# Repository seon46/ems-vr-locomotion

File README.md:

# EMS-VR Locomotion Interface

座位VRユーザーに擬似的な歩行感覚を生成するロコモーションインターフェースの研究プロジェクト。
6チャンネルの下肢EMS（電気筋刺激）と足裏振動を歩行アニメーションに同期させることで、座ったままでも「歩いている」と感じられる体験を目指す。

**埼玉大学大学院 理工学研究科 数理電子情報系専攻 / Parinya Lab — 遠藤 瀬音（Endo Seno）**

## 概要

本研究では、VR空間内の歩行アニメーションに合わせて下肢の筋肉にEMSを与え、歩行に伴う筋収縮感覚を再現する座位向けロコモーションインターフェースを開発しています。

先行研究 LegSense（Um et al., UIST 2024）の歩行感覚EMS提示をベースに、VRアバターのスタミナ低下に連動した疲労感の演出へ拡張することを目指しています。

### 実装済みの機能

- **6チャンネルEMS歩行同期**: Battye et al. (1966) の筋活動データに基づき、歩行アニメーションのNormalized Timeから各筋の収縮タイミングでEMSを発火
- **足裏振動フィードバック**: 4チャンネル（両足の踵・前足部）のERMモーターによる接地感の提示（ファームウェア実装済み、Unity側は未統合）
- **VR歩行環境**: 手続き的生成の廊下シーン、鏡による自己アバター視認、歩行同期のhead bob、足音再生

### 安全基準

- 出力上限: ≤ 10 mA RMS、≤ ±50 V
- 1回の発火は最大1秒（ファームウェアで制限）
- ヒトへの適用前にIRB承認を取得予定

## システム構成

```
┌─────────────────────────────────────────────────────────────┐
│  Unity (PC)                                                 │
│  ├── VR Scene (Meta Quest 3S via Quest Link)                │
│  ├── Walking Animation (Mixamo)                             │
│  ├── EMSTrigger.cs (Normalized Time → 筋活動タイミング発火)  │
│  └── UDP Broadcast (192.168.11.255:8266)                    │
│       ├── "FIRE,l1,l2,l3,l4,l5,l6"  (EMS, Level 0〜15)    │
│       └── "VIB,rh,rf,lh,lf"         (振動, PWM 0〜255)    │
└──────────┬──────────────────────────┬───────────────────────┘
           │                          │
    ┌──────▼──────┐          ┌────────▼────────┐
    │ EMS Module  │          │ Vibration Motor │
    │ ×6 units    │          │ Controller      │
    │             │          │                 │
    │ XIAO        │          │ ESP32 HUZZAH32  │
    │ ESP32-C3    │          │ + IRLZ44N ×4   │
    │ + AC_TENS   │          │ + ERM ×4       │
    │ SHOCK v2    │          │ (Adafruit 1201) │
    └─────────────┘          └─────────────────┘
    大腿四頭筋 (L/R)          右かかと / 右つま先
    ハムストリングス (L/R)     左かかと / 左つま先
    前脛骨筋 (L/R)
```

## ハードウェア

### EMS刺激モジュール（6ch）

| コンポーネント | 説明 |
|---|---|
| XIAO ESP32-C3 × 6 | マイコン（WiFi/UDP受信、IP固定: 192.168.11.101〜106） |
| AC_TENS SHOCK MODULE v2 × 6 | EMS出力モジュール |
| キャリアボード × 6 | KiCad設計、JLCPCB製造 |

### 振動フィードバック（4ch）

| コンポーネント | 説明 |
|---|---|
| Adafruit HUZZAH32 (ESP32 Feather) | マイコン（WiFi/UDP受信・PWM出力） |
| IRLZ44N N-ch MOSFET × 4 | モータードライバ |
| Adafruit 1201 ERM Motor × 4 | φ10mm コイン型振動モーター |
| 1N4148 ダイオード × 4 | フライバック保護 |

### VR

| コンポーネント | 説明 |
|---|---|
| Meta Quest 3S | HMD（Quest Link接続） |
| Unity 6.5 | ゲームエンジン |

## ディレクトリ構成

```
ems-vr-locomotion/
├── README.md
├── unity/
│   └── Scripts/
│       ├── GaitTiming.cs          # 歩行位相の共有プロバイダ（全スクリプトが参照）
│       ├── EMSTrigger.cs          # Normalized Time → EMS発火 (UDP FIRE)
│       ├── FootstepAudio.cs       # 踵接地タイミングで足音再生
│       ├── HeadFollow.cs          # 首支点のVRカメラ追従 + 歩行同期head bob
│       ├── WalkInput.cs           # XRコントローラー/キーボードによる移動入力
│       ├── VRIKTargetFollower.cs  # XRハンドトラッキング → IKターゲット追従
│       ├── CorridorGenerator.cs   # 手続き的生成の廊下シーン
│       ├── MirrorReflection.cs    # 平面鏡反射カメラ（自己アバター視認用）
│       └── GaitDiagnostics.cs     # 踵接地位相の実測ツール
├── firmware/
│   ├── ems_trigger/               # EMS制御ファームウェア (PlatformIO/ESP32-C3)
│   │   └── main.cpp
│   └── vibration_motor/           # 足裏振動モーターファームウェア (Arduino/ESP32)
│       └── vibration_4motor.ino
├── hardware/
│   └── carrier_board/             # EMSキャリアボード基板設計データ (KiCad)
│       └── Gerber/                # 製造用ガーバーファイル
└── tools/
    └── udp_test_send.py           # EMS UDPテスト送信ツール (Python)
```

## 通信プロトコル

WiFiネットワーク上でUDPブロードキャストを使用:

| 項目 | 内容 |
|---|---|
| ポート | 8266 |
| EMS発火 | `FIRE,l1,l2,l3,l4,l5,l6` — 各チャンネルのLevel (0〜15) |
| 振動制御 | `VIB,rh,rf,lh,lf` — 各モーターのPWM強度 (0〜255) |
| デバイス探索 | `WHO` → 各デバイスがID・IP・パラメータを返信 |

各EMSデバイスはWebUI（HTTP）でパルス幅・周波数・刺激時間のパラメータを設定できる。

## 今後の予定

- 足裏振動のUnity側統合（ファームウェアは実装済み）
- スタミナ連動型の疲労感演出の設計・実装（歩行パターンの劣化 + クロスモーダル知覚による疲労感の表現）
- オシロスコープによる出力波形の安全性検証
- IRB申請・承認
- ユーザースタディの設計・実施

## 先行研究

- Um, L. et al. (2024). **LegSense**: Inducing Walking Sensation in Seated VR by Electrical Muscle Stimulation. *ACM UIST 2024*.
- Takahashi, A. et al. (2022). Increasing a Seated Passenger's Walking Sensation Using EMS. *Frontiers in VR*.
- Ota, S. et al. (2024). The Effect of Electrical Muscle Stimulation on Foot Pressure Distribution and Walking Sensation in Passive Walking in Seated VR. *Frontiers in VR*.
- Battye, C.K. & Joseph, J. (1966). An investigation by telemetering of the activity of some muscles in walking. *Medical & Biological Engineering*.

## ライセンス

研究用プロジェクト。コードの再利用については著者にお問い合わせください。

## 著者

**遠藤 瀬音 / Endo Seno**
埼玉大学大学院 理工学研究科 数理電子情報系専攻（M1）
Parinya Lab

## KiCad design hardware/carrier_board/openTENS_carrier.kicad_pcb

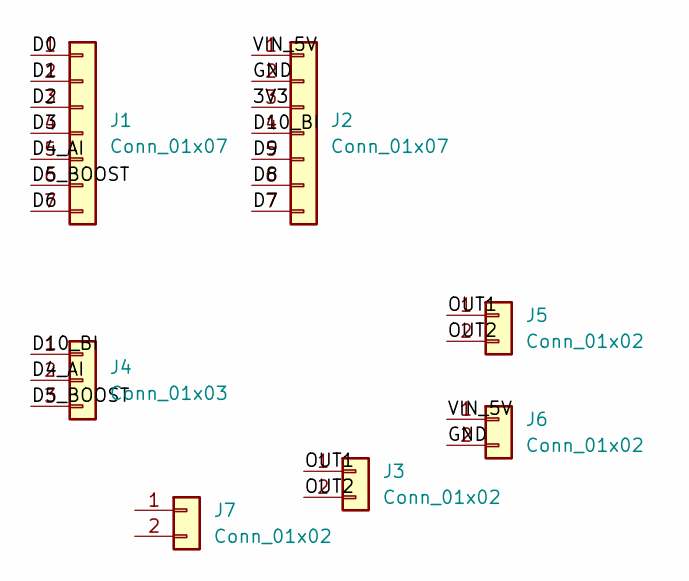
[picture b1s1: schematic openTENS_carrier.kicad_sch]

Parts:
J1, J2: Conn_01x07; PinHeader_1x07_P2.54mm_Vertical
J3, J5, J6, J7: Conn_01x02; PinHeader_1x02_P2.54mm_Vertical
J4: Conn_01x03; PinHeader_1x03_P2.54mm_Vertical

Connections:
/3V3: J2.3
/D0: J1.1
/D1: J1.2
/D2: J1.3
/D3: J1.4
/D4_AI: J1.5, J4.2
/D5_BOOST: J1.6, J4.3
/D6: J1.7
/D7: J2.7
/D8: J2.6
/D9: J2.5
/D10_BI: J2.4, J4.1
/GND: J2.2, J6.2
/OUT1: J3.1, J5.1
/OUT2: J3.2, J5.2
/VIN_5V: J2.1, J6.1

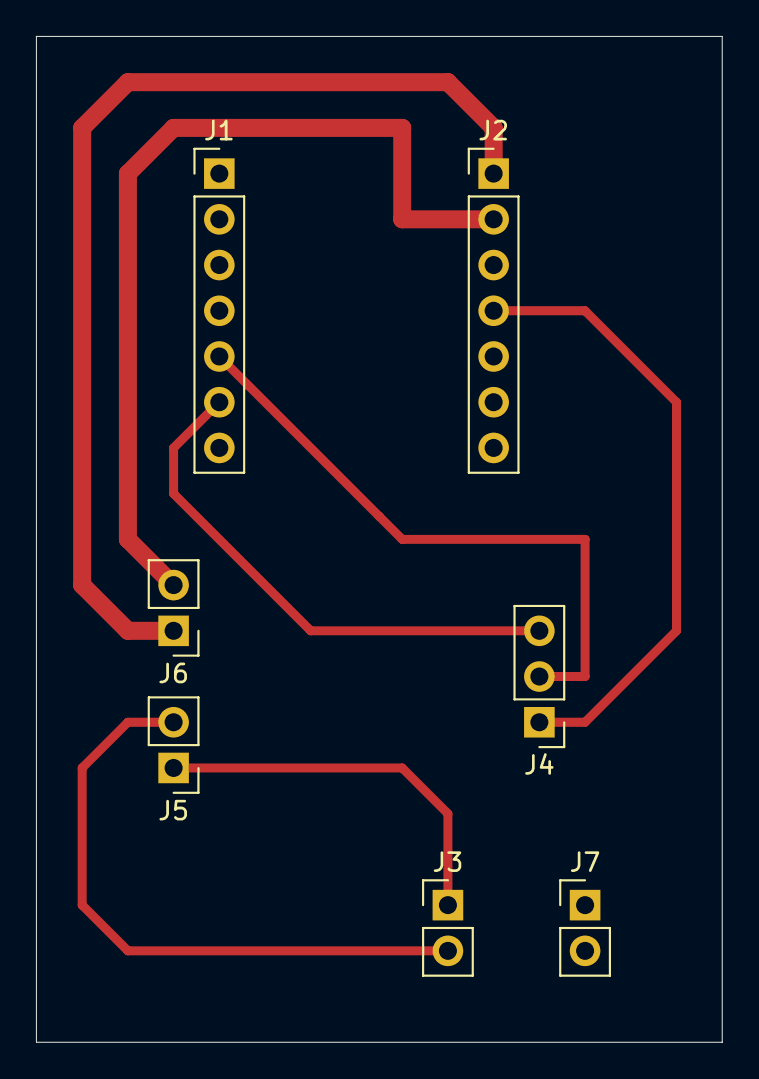
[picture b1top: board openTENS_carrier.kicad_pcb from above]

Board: 2 copper layers, 38.1 x 55.9 mm, 7 parts (0 on the bottom side), 7 nets.
